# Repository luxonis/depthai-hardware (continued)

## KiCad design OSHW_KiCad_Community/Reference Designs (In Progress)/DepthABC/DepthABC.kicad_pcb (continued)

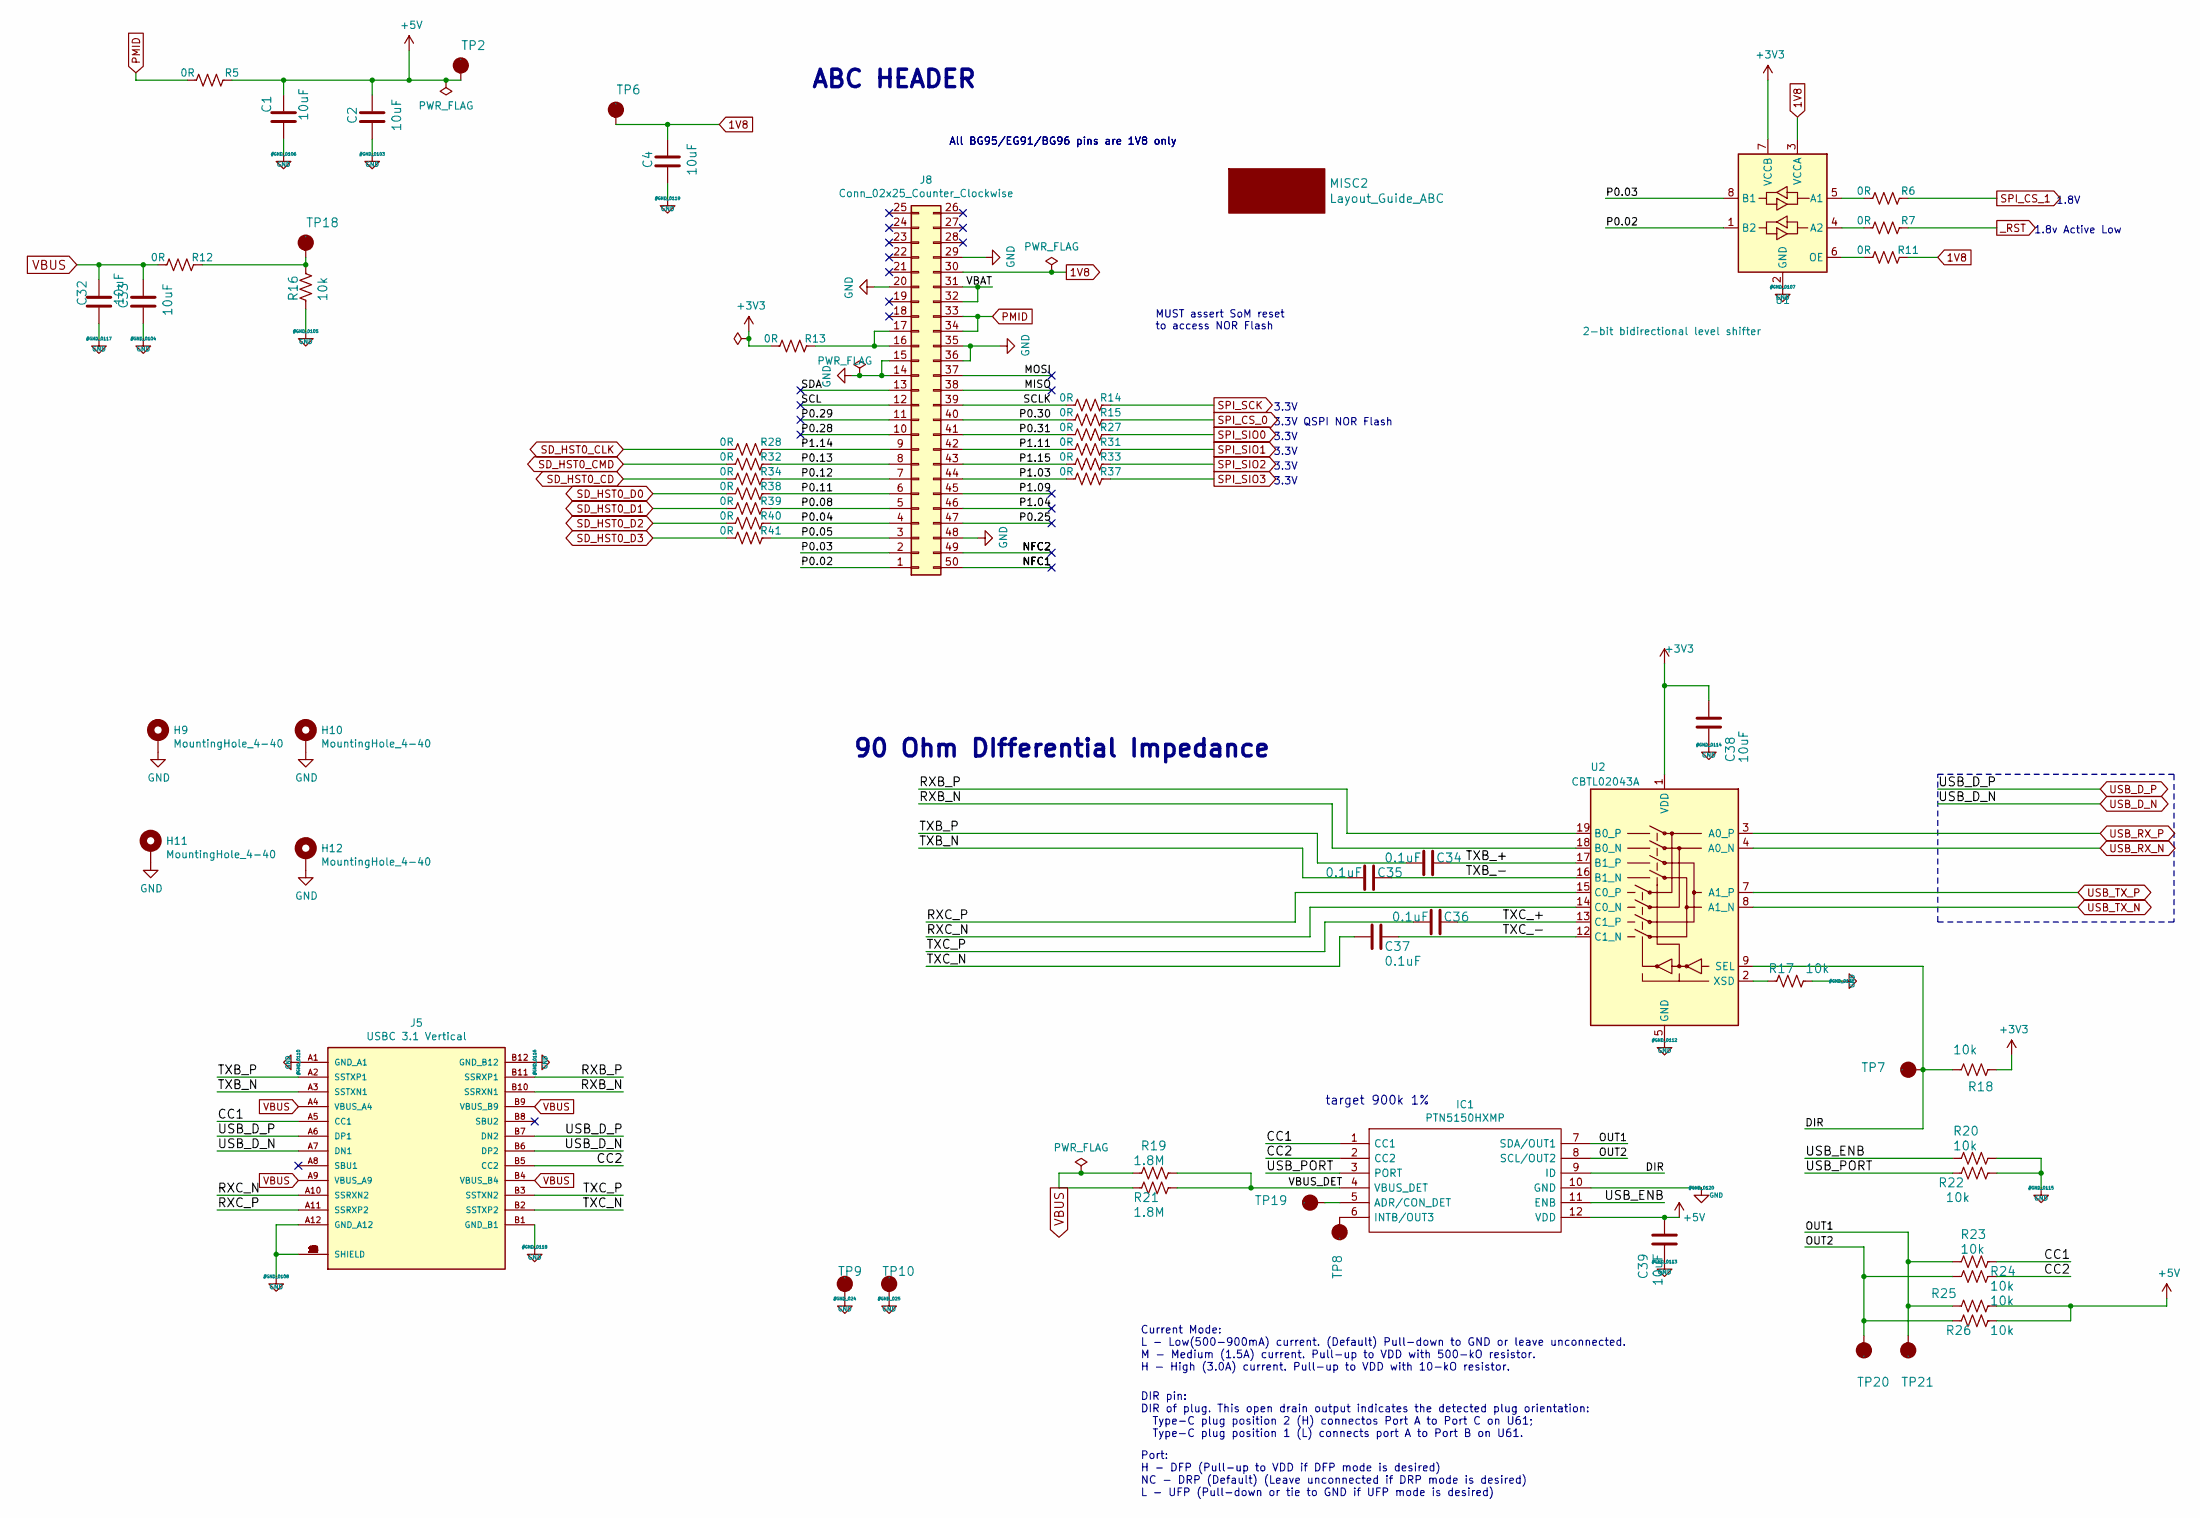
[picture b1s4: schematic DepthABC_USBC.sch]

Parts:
C1, C2, C4, C32, C33, C38, C39: 10uF; C_0603_1608Metric; Voltage Rating 6.3V; MPN1 C0603C106M8PAC7867
C34, C35, C36, C37: 0.1uF; C_0603_1608Metric; Voltage Rating 10V; MPN1 C0603C104K8RACTU
H9, H10, H11, H12: MountingHole_4-40; MountingHole_3mm_Pad
IC1: PTN5150HXMP; Manufacturer_Part_Number PTN5150HXMP; Mouser Part Number 771-PTN5150HXMP
J5: USBC 3.1 Vertical; AMPHENOL_10132328-10011LF; PARTREV A
J8: Conn_02x25_Counter_Clockwise; DF23C-50DS-0.5V(51); MPN1 DF23C-50DS-0.5V(51)
MISC2: Layout_Guide_ABC; ABC-Layout
R5, R6, R7, R11, R12, R13, R14, R15, R27, R28, R31, R32, R33, R34, R37, R38, R39, R40, R41: 0R; R_0603_1608Metric; Voltage Rating 1/10W; MPN1 RC0603FR-070RL
R16, R17, R18, R20, R22, R23, R24, R25, R26: 10k; R_0603_1608Metric; Voltage Rating 1/10W; MPN1 RC0603FR-7W10KL
R19, R21: 1.8M; R_0603_1608Metric; Voltage Rating 1/10W
TP2, TP6, TP7, TP8, TP9, TP10, TP18, TP19, TP20, TP21: TestPoint_Pad_D2.0mm
U1: 2-bit bidirectional level shifter; TSSOP-8_3x3mm_P0.65mm; MPN1 NTB0102DP-Q100H
U2: CBTL02043A; WQFN-20-1EP_2.5x4.5mm_P0.5mm_EP1x2.9mm; MPN1 CBTL02043ABQ,115

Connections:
1V8: C4.2, J8.30, R11.1, TP6.1, U1.3 (VCCA); also elsewhere on the board
+5V: C1.1, C2.2, C39.1, IC1.12 (VDD), R5.1, R25.1, R26.1, TP2.1; also elsewhere on the board
/USBC&POWER/CC1: IC1.1 (CC1), J5.A5 (CC1), R23.1
/USBC&POWER/CC2: IC1.2 (CC2), J5.B5 (CC2), R24.1
/USBC&POWER/DIR: IC1.9 (ID), R18.2, TP7.1, U2.9 (SEL)
/USBC&POWER/MISO: J8.38
/USBC&POWER/MOSI: J8.37
/USBC&POWER/NFC1: J8.50
/USBC&POWER/NFC2: J8.49
/USBC&POWER/OUT1: IC1.7 (SDA/OUT1), R23.2, R25.2, TP21.1
/USBC&POWER/OUT2: IC1.8 (SCL/OUT2), R24.2, R26.2, TP20.1
/USBC&POWER/P0.02: J8.1, U1.1 (B2)
/USBC&POWER/P0.03: J8.2, U1.8 (B1)
/USBC&POWER/P0.04: J8.4, R40.1
/USBC&POWER/P0.05: J8.3, R41.1
/USBC&POWER/P0.08: J8.5, R39.1
/USBC&POWER/P0.11: J8.6, R38.1
/USBC&POWER/P0.12: J8.7, R34.1
/USBC&POWER/P0.13: J8.8, R32.1
/USBC&POWER/P0.25: J8.47
/USBC&POWER/P0.28: J8.10
/USBC&POWER/P0.29: J8.11
/USBC&POWER/P0.30: J8.40, R15.2
/USBC&POWER/P0.31: J8.41, R27.2
/USBC&POWER/P1.03: J8.44, R37.2
/USBC&POWER/P1.04: J8.46
/USBC&POWER/P1.09: J8.45
/USBC&POWER/P1.11: J8.42, R31.2
/USBC&POWER/P1.14: J8.9, R28.1
/USBC&POWER/P1.15: J8.43, R33.2
/USBC&POWER/RXB_N: J5.B10 (SSRXN1), U2.18 (B0_N)
/USBC&POWER/RXB_P: J5.B11 (SSRXP1), U2.19 (B0_P)
/USBC&POWER/RXC_N: J5.A10 (SSRXN2), U2.14 (C0_N)
/USBC&POWER/RXC_P: J5.A11 (SSRXP2), U2.15 (C0_P)
/USBC&POWER/SCL: J8.12
/USBC&POWER/SCLK: J8.39, R14.2
/USBC&POWER/SDA: J8.13
/USBC&POWER/TXB_+: C34.1, U2.17 (B1_P)
/USBC&POWER/TXB_-: C35.1, U2.16 (B1_N)
/USBC&POWER/TXB_N: C35.2, J5.A3 (SSTXN1)
/USBC&POWER/TXB_P: C34.2, J5.A2 (SSTXP1)
/USBC&POWER/TXC_+: C36.1, U2.13 (C1_P)
/USBC&POWER/TXC_-: C37.1, U2.12 (C1_N)
/USBC&POWER/TXC_N: C37.2, J5.B2 (SSTXP2)
/USBC&POWER/TXC_P: C36.2, J5.B3 (SSTXN2)
/USBC&POWER/USB_ENB: IC1.11 (ENB), R20.2
/USBC&POWER/USB_PORT: IC1.3 (PORT), R22.2
/USBC&POWER/VBAT: J8.31, J8.32
/USBC&POWER/VBUS_DET: IC1.4 (VBUS_DET), R19.1, R21.1
unnamed: IC1.5 (ADR/CON_DET), TP19.1
unnamed: IC1.6 (INTB/OUT3), TP8.1
unnamed: J8.16, J8.17, R13.1
unnamed: R6.2, U1.5 (A1)
unnamed: R7.2, U1.4 (A2)
unnamed: R11.2, U1.6 (OE)
unnamed: R12.1, R16.2, TP18.1
unnamed: R17.2, U2.2 (XSD)
PMID: J8.33, J8.34, R5.2
SD_HST0_CD: R34.2; also elsewhere on the board
SD_HST0_CLK: R28.2; also elsewhere on the board
SD_HST0_CMD: R32.2; also elsewhere on the board
SD_HST0_D0: R38.2; also elsewhere on the board
SD_HST0_D1: R39.2; also elsewhere on the board
SD_HST0_D2: R40.2; also elsewhere on the board
SD_HST0_D3: R41.2; also elsewhere on the board
SPI_CS_0: R15.1; also elsewhere on the board
SPI_CS_1: R6.1; also elsewhere on the board
SPI_SCK: R14.1; also elsewhere on the board
SPI_SIO0: R27.1; also elsewhere on the board
SPI_SIO1: R31.1; also elsewhere on the board
SPI_SIO2: R33.1; also elsewhere on the board
SPI_SIO3: R37.1; also elsewhere on the board
USB_D_N: J5.A7 (DN1), J5.B6 (DP2); also elsewhere on the board
USB_D_P: J5.A6 (DP1), J5.B7 (DN2); also elsewhere on the board
USB_RX_N: U2.4 (A0_N); also elsewhere on the board
USB_RX_P: U2.3 (A0_P); also elsewhere on the board
USB_TX_N: U2.8 (A1_N); also elsewhere on the board
USB_TX_P: U2.7 (A1_P); also elsewhere on the board
VBUS: C32.1, C33.2, J5.A4 (VBUS_A4), J5.A9 (VBUS_A9), J5.B4 (VBUS_B4), J5.B9 (VBUS_B9), R12.2, R19.2, R21.2; also elsewhere on the board
_RST: R7.1; also elsewhere on the board

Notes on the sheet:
target 900k 1%
Current Mode: L - Low(500-900mA) current. (Default) Pull-down to GND or leave unconnected. M - Medium (1.5A) current. Pull-up to VDD with 500-kO resistor. H - High (3.0A) current. Pull-up to VDD with 10-kO resistor.
DIR pin: DIR of plug. This open drain output indicates the detected plug orientation: Type-C plug position 2 (H) connectos Port A to Port C on U61; Type-C plug position 1 (L) connects port A to Port B on U61.
Port: H - DFP (Pull-up to VDD if DFP mode is desired) NC - DRP (Default) (Leave unconnected if DRP mode is desired) L - UFP (Pull-down or tie to GND if UFP mode is desired)
All BG95/EG91/BG96 pins are 1V8 only
ABC HEADER
1.8V
3.3V
QSPI NOR Flash
MUST assert SoM reset to access NOR Flash
1.8v Active Low
90 Ohm DIfferential Impedance

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
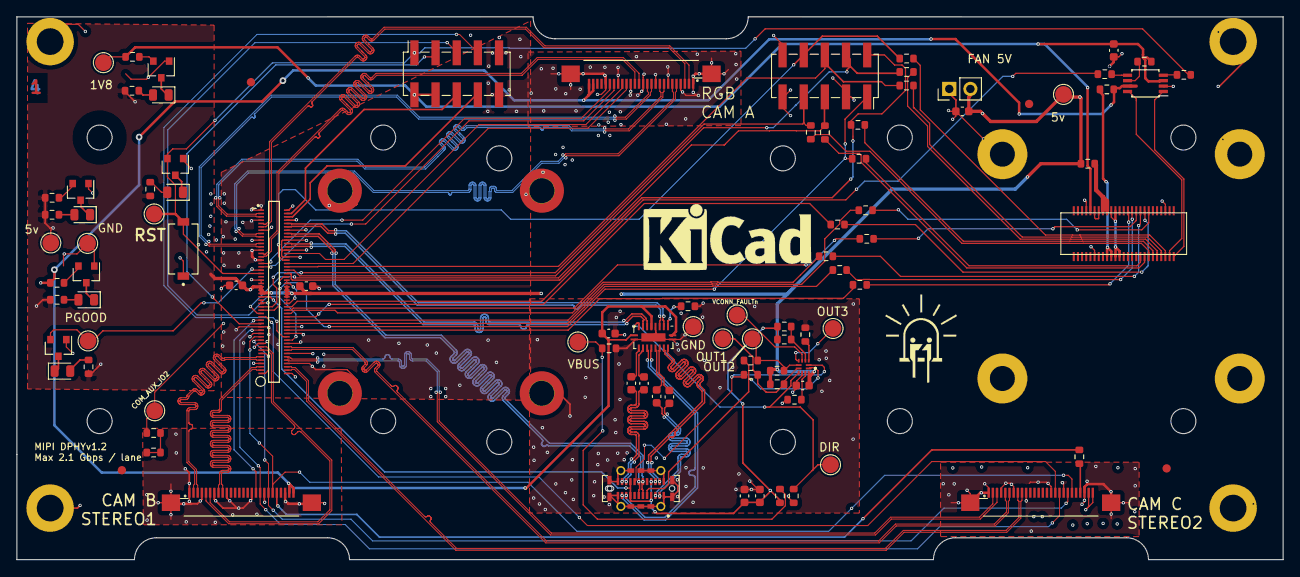
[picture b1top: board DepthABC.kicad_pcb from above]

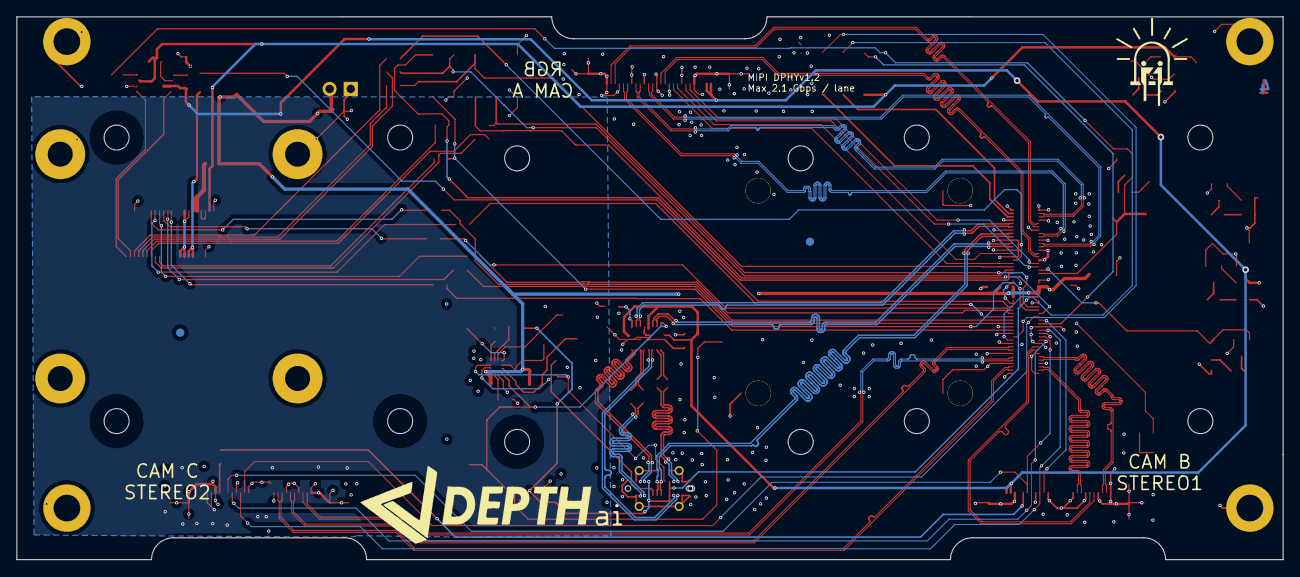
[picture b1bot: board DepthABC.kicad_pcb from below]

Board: 4 copper layers, 152.0 x 65.2 mm, 113 parts (5 on the bottom side), 125 nets.

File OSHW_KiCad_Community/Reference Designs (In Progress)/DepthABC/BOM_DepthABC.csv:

Component Count:,99,,,,,,,,,,,,
,,,,,,,,,,,,,
,,,,,,,,,,,,,
Collated Components:,,,,,,,,,,,,,
,,,,,,,,,,,,,
Item,Qty,Reference(s),Value,Footprint,Datasheet,Link1,MANUFACTURER,MPN1,Population,STANDARD,Short Description,Substitutes ,Voltage Rating
1,1,B1,"Off-Mohm, 50mA",depthABC:SW_PTS636_SM43J_SMTR_LFS,~,https://www.digikey.com/en/products/detail/c-k/PTS636-SM43-S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,C&K,PTS636,Y,~,reset switch,OR EQUIVALENT,~
2,8,"C1, C2, C3, C4, C32, C33, C38, C39",10uF ,Capacitor_SMD:C_0603_1608Metric,~,https://www.digikey.com/en/products/detail/kemet/C0603C106M8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,Kemet,C0603C106M8PAC7867,Y,X5R 20%,~,OR EQUIVALENT,6.3V
3,4,"C34, C35, C36, C37",0.1uF,Capacitor_SMD:C_0603_1608Metric,~,https://www.digikey.com/en/products/detail/kemet/C0603C104K8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,Kemet,C0603C104K8RACTU,Y,X5R 10%,~,OR EQUIVALENT,10V
4,3,"CAM1, CAM2, CAM3",Arducam_Module,Luxonis_KiCad_Master:arducam_40mm_34mm,~,~,Arducam,~,NO POP,~,~,~,~
5,3,"D1, D4, D5",RED,LED_SMD:LED_0805_2012Metric,~,https://www.digikey.com/en/products/detail/kingbright/APT201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,Kingbright,APT2012SRCPRV,Y,~,2V 0805 20mA test red LED,OR EQUIVALENT,~
6,2,"D2, D3",YELLOW,LED_SMD:LED_0805_2012Metric,~,https://www.digikey.com/en/products/detail/kingbright/APT201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,Kingbright,APT2012SYCK/J3-PRV,Y,~,2V 0805 20mA test orange LED,OR EQUIVALENT,~
7,6,"FID1, FID2, FID3, FID4, FID5, FID6",Fiducial,Fiducial:Fiducial_1mm_Mask2mm,~,~,~,~,~,~,~,~,~
8,4,"H1, H2, H3, H4",MountingHole_M3,MountingHole:MountingHole_3.2mm_M3_ISO7380_Pad,~,~,~,~,NO POP,~,Arducam mounts,~,~
9,4,"H5, H6, H7, H8",MountingHole_Pad,Luxonis_KiCad_Master:Mounting_Wuerth_WA-SMSI-M2_H3mm_9774030243,~,https://www.digikey.com/en/products/detail/9774030243R/732-7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,Wuerth,9774030243R,Y,~,SoM Mount,~,~
10,4,"H9, H10, H11, H12",MountingHole_4-40,MountingHole:MountingHole_3mm_Pad,~,~,~,~,NO POP,~,ABC mount,~,~
11,1,IC1,PTN5150HXMP,Luxonis_KiCad_Master:PTN5150HXMP,http://www.nxp.com/docs/en/data-sheet/PTN5150A.pdf,https://www.digikey.com/en/products/detail/nxp-usa-inc/PTN51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,NXP,PTN5150HXMP,Y,~,Usb port control,N,
12,2,"J1, J4",Conn_02x05_Odd_Even,Connector_PinSocket_2.54mm:PinSocket_2x05_P2.54mm_Vertical_SMD,~,~,~,~,NO POP,~,2x05 FEMALE 2.54mm pin socket,~,~
13,1,J2,FAN,Connector_PinHeader_2.54mm:PinHeader_1x02_P2.54mm_Vertical,~,~,~,~,NO POP,~,~,~,~
14,1,J3,BW1099EMB_SoM,Luxonis_KiCad_Master:DF40HC(3.0)-100DS-0.4V(58),https://www.hirose.com/product/document?clcode=CL0684-4003-3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,https://www.mouser.com/ProductDetail/Hirose-Connector/DF40HC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,Amphenol,DF40HC(3.0)-100DS-0.4V(58),Y,~,SoM header,N,~
15,1,J5,USBC 3.1 Vertical,AMPHENOL_10132328-10011LF,,https://www.amphenol-icc.com/usb-1013232810011lf.html?__cf_c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,Amphenol,10132328-10011LF,Y,~,~,N,~
16,3,"J6, J7, J9",26_pin_FFC,Luxonis_KiCad_Master:F32R-26p-FFC,,https://www.mouser.com/ProductDetail/Amphenol-ICC-Aorora/F32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,Amphenol,F32R-1A7H1-11026,Y,~,DM Series Luxonis FFC,N,~
17,1,J8,Conn_02x25_Counter_Clockwise,ABC:DF23C-50DS-0.5V(51),~,https://www.mouser.com/ProductDetail/Hirose-Connector/DF23C-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,Amphenol,DF23C-50DS-0.5V(51),Y,~,ABC header,N,~
18,1,MISC1,Layout_Guide_BW1099,Luxonis_KiCad_Master:BW1099_Layout_Guide,~,~,Luxonis,~,NO POP,~,~,~,~
19,1,MISC2,Layout_Guide_ABC,ABC:ABC-Layout,~,~,Luxonis,~,NO POP,~,~,~,~
20,5,"Q1, Q2, Q3, Q4, Q5",RK7002B,Package_TO_SOT_SMD:SOT-23,https://media.digikey.com/pdf/Data%20Sheets/Rohm%20PDFs/RK7002B.pdf,https://www.digikey.com/en/products/detail/rohm-semiconducto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,ROhm,,Y,~,2.5V Drive Nch FET ESD Protection Diode,W/ APPROVAL,60V 250mA
21,6,"R1, R2, R3, R4, R30, R36",10,Resistor_SMD:R_0603_1608Metric,~,https://www.digikey.com/en/products/detail/rohm-semiconducto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,ROhm,ESR03EZPF10R0,Y,1%,~,OR EQUIVALENT,1/10W
22,21,"R5, R6, R7, R9, R10, R11, R12, R13, R14, R15, R27, R28, R31, R32, R33, R34, R37, R38, R39, R40, R41",0R,Resistor_SMD:R_0603_1608Metric,~,https://www.digikey.com/en/products/detail/yageo/RC0603FR-07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,Yageo,RC0603FR-070RL,Y,~,~,OR EQUIVALENT,1/10W 
23,10,"R8, R16, R17, R18, R20, R22, R23, R24, R25, R26",10k,Resistor_SMD:R_0603_1608Metric,~,https://www.digikey.com/en/products/detail/yageo/RC0603FR-7W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,Yageo,RC0603FR-7W10KL,Y,1%,~,OR EQUIVALENT,1/10W 
24,2,"R19, R21",1.8M,Resistor_SMD:R_0603_1608Metric,~,~,~,~,Y,1%,~,OR EQUIVALENT,1/10W
25,2,"R29, R35",1k,Resistor_SMD:R_0603_1608Metric,~,https://www.digikey.com/en/products/detail/koa-speer-electro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,KOA,SG73S1JTTD1001F,Y,1%,~,OR EQUIVALENT,1/10W
26,1,U1,2-bit bidirectional level shifter ,Package_SO:TSSOP-8_3x3mm_P0.65mm,http://www.ti.com/lit/ds/symlink/txb0102.pdf,https://www.digikey.com/en/products/detail/nxp-usa-inc/NTB01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,NXP,NTB0102DP-Q100H,Y,~,~,OR EQUIVALENT,~
27,1,U2,CBTL02043A,Package_DFN_QFN:WQFN-20-1EP_2.5x4.5mm_P0.5mm_EP1x2.9mm,https://www.nxp.com/docs/en/data-sheet/CBTL02043A_CBTL02043B.pdf,https://www.digikey.com/en/products/detail/nxp-usa-inc/CBTL0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,NXP,"CBTL02043ABQ,115",Y,~,Usb mux,N,

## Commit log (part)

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2023-01-07 Typo fix
2023-01-07 boot mode fix eMMC
2023-01-16 new datasheet
2023-01-16 OAK-SoM MAX updates
2023-01-18 Added mqtt support to POE docs
2023-01-18 Removed multi-cam-support branch from docs
2023-01-19 Update ar0234.rst
    Tested on FFC-4P and we seem to support 60 FPS.
2023-01-23 Fixed max FPS for IMX214 from 60fps to 35fps
2023-01-23 Update NG9097pro.rst
    broken link fix
2023-01-24 Projector temeprature update docs
2023-01-24 Updated LCM48/IMX582 docs
2023-01-24 Updated CCM specs
2023-01-25 Fixed M8 usb connection description
2023-01-25 Added HW blocks docs for RVC2
2023-01-26 Added OAK FFC Kit to docs. Renamed file
2023-01-30 Updated products' key features
2023-02-01 Updated poe s2 connectors in docs
2023-02-04 Added advance poe settings docs
2023-02-04 Added docs on AF/FF querying info with depthai
2023-02-06 Fixed some urls/refs, removed copyright
2023-02-08 Added poe injector to the list of docs
2023-02-11 broken sentence rmoved
2023-02-13 removed pdf building RTD - potentially fixing failing docs build
2023-02-14 SR and LR added to OAK-D CE
2023-02-14 new photos
2023-02-14 TODO: add redirections for /index.html#all-in-one-dev-kit-designs and /index.html#miscellaneous-designs to /index.html#other-designs
2023-02-14 new thumbnails
2023-02-14 cropped images
2023-02-14 bg removed
2023-02-15 Added oak-d-pro TH img
2023-02-15 Temp fix for oak-d-pro thumbnail pic
2023-02-16 photo swap
2023-02-17 Updated performance docs
2023-02-20 Updated favicon
2023-02-21 OAK-D-LR & SR added to index
2023-02-22 Updated calibration docs
2023-02-28 Updated the files to R3M1E4
2023-03-01 Updated oak-d-sr minZ
    (cherry picked from commit 54b8ce719f3469f9dd66256d9fc4b3c52be31205)
2023-03-04 Updated supported sensors docs
2023-03-06 Updated time diagrams for FSYNC
2023-03-06 Added code snippet for FFC-4P syncing between 4-lane and 2-lane MIPI groups
2023-03-08 Upload OAK-D-S2 enclosure stl files
2023-03-08 Upload OAK-D_enclosure stp file
2023-03-08 Upload OAK-D-LITE_enclosure stp file
2023-03-08 Upload OAK-1_enclosure STL file
2023-03-08 Upload OAK-1-POE-enclosure STL file
2023-03-08 Upload OAK-1-Lite_enclosure .STL file
2023-03-08 Upload OAK-D-S2-POE_enclosure.STL file
2023-03-08 Upload OAK-D-CM4-POE_enclosure.STL file
2023-03-08 Upload y-adapter.STL file
2023-03-08 Added IMX582-RAM doc snippet to OAK-1-Max and IMX582 docs pages
2023-03-14 Updated depth perception (minz/maxz/optimal) for all OAK-D* models
2023-03-15 Updated rvc3 docs (main features)
2023-03-22 updated oak-d-lite encsloure
2023-03-27 Updated device features (rvc2) for OAK-1 cams
2023-03-27 Updated supported sensors page, added IMX296, IMX219
2023-04-03 correction connector A pin32 -- RTC_INT
2023-04-03 Updated docs so ov9782 supports 400p (120fps)
2023-04-04 Add shop link for OAK-D-PCBA
2023-04-04 Added docs on how to replace oak som pro versions
2023-04-11 Updated OAK-D-LR FOV values
2023-04-19 Update calibration.rst
    Update calibration.rst with new calibration process
2023-04-21 Fixing ext trigger schematics
2023-04-25 Added FFC-Kit adapters
2023-04-26 merged SPI and RTC fixes
2023-04-26 SOM PRO - added note that changing rvc2 to rvc3 not officially supported by Luxonis
2023-05-05 Added imgs to docs
2023-05-05 Added OAK-FFC-4P-POE docs page. Moved FFC-6P to other devices
2023-05-06 Updated OAK-FFC 1P PoE page and images
2023-05-08 Added docs section about using RPI cameras to FFC baseboards
2023-05-10 Fix IMX582 HFOV / DFOV
2023-05-11 Moved enclosure files (step/stl) to digitalocean as well (previously it was only PCBAs)
2023-05-18 128Mbit NOR
2023-05-19 Initial release of OAK-D-SR-POE
2023-05-19 Added OAK-D-SR-POE docs
2023-05-23 Uploaded FFC-6P and FFC-4P-POE adapters for FFC-Kit
2023-06-02 Updated imgs
2023-06-02 OAK-D-Lite thermal tests
2023-06-03 Added CCM thermal heating to docs
2023-06-04 Updated docs, added link
2023-06-13 Updated FFC-6P docs (dimensions & weight)
2023-06-14 Updated readthedocs.yaml
2023-06-14 Updated yaml
2023-06-14 Revert "Updated yaml"
    This reverts commit 0b040243d894fd137d77818ec4c8efbec9f4ca6e.
2023-06-14 Updated max FPS at 720p and 800p for OV9x82 sensors, as support was added for 120fps (previously max 60fps)
2023-06-19 Updated dot projector docs
2023-06-20 PoE device USB2.0 spcs fix
2023-06-21 Added img
2023-06-22 Added low-light comparison photo
2023-06-23 trd yaml update
2023-06-26 Updated sensor resolution modes in docs
2023-06-26 Added initial release of PA0960_R0M0E0 of FFC-IR
2023-06-26 Updated DM0260 to revision R2M1E1
    Missing pictures of new revision boards.
2023-06-27 Added .STEP 3d model to 3D_Models folder
2023-06-27 Update README.md, changed Altium designer from 22 to 23
2023-06-27 Added BOM files to DOCS
    Added BOM files to projects:
    - PA0960
    - DM0260 for 1V0 and 1V2
    - OAK-D-SR-PoE for EL2086 and EL6905
2023-06-30 Updated FFC camera modules images
2023-07-03 Enable pdf generation
2023-07-05 Add files via upload
    added enclosure step file
2023-07-06 Removed unicode '❌' as it fails to render to PDF
2023-07-24 Update OV9282 FOV (89 DFOV, 80HFOV)
2023-07-26 Fixed typo, update oak-d-pro-w-poe img
2023-08-01 Updated POE troubleshooting
2023-08-16 Updated readthedocs.yaml, as they decided to deprecate some functions yet again for absolutely no good reason
2023-08-16 Updated available CCMs page
2023-08-24 Updated docs for oak-ffc-4p-poe
2023-09-01 Files for M8 programming board, fabricaation files in folder Docs, PCB in forder PCB
2023-09-01 Initial push
    Added Production files in the folder Docs. Added PCB files in folder PCB. Added .STEP of DM370
2023-09-01 Updated SOM-PRO NOR flash to 32MB
2023-09-01 Updated CCMs used for mono cameras in Pro devices
2023-09-01 Fixed old revision of Schematic.pdf and added files from GDrive to be shure it is the latest revision
2023-09-01 updated readme, referencing DM0260
2023-09-01 Updated docs to include some additional HW docs, fixed formatting, specified factory reset info
2023-09-05 Added rae readme
2023-09-05 Updated charuco boards
2023-09-13 Updated OAK-D-LR 3D models
2023-09-18 Update docs
2023-09-20 Remove distortion params, as we do on-device undistortion/dewarping
2023-09-25 Update rvc4 AI performance/power ocnsumption
2023-09-28 Update AR0234 driver specs, as we have updated driver on develop branch
2023-10-03 Bump urllib3 from 1.26.15 to 1.26.17 in /docs
    Bumps [urllib3](https://github.com/urllib3/urllib3) from 1.26.15 to 1.26.17.
    - [Release notes](https://github.com/urllib3/urllib3/releases)
    - [Changelog](https://github.com/urllib3/urllib3/blob/main/CHANGES.rst)
    - [Commits](https://github.com/urllib3/urllib3/compare/1.26.15...1.26.17)
    ---
    updated-dependencies:
2023-10-03 Added FOV calc links to RAE, and to all Rectified Depth FOV
2023-10-09 Update CCM section
2023-10-11 Updated FFC-4P docs
2023-10-18 Bump urllib3 from 1.26.15 to 1.26.18 in /docs
    Bumps [urllib3](https://github.com/urllib3/urllib3) from 1.26.15 to 1.26.18.
    - [Release notes](https://github.com/urllib3/urllib3/releases)
    - [Changelog](https://github.com/urllib3/urllib3/blob/main/CHANGES.rst)
    - [Commits](https://github.com/urllib3/urllib3/compare/1.26.15...1.26.18)
    ---
    updated-dependencies:
2023-10-20 Added power usage docs to all rvc2 devices
2023-10-20 Added max operating temp to all rvc2 devices
2023-10-21 RPI 15pin adapter
    Added project files for OAK-FFC to 15pin RPI FFC adapter
2023-10-23 adapter connection
    added connection photo
2023-10-23 Uploaded model to DO
2023-10-23 Moved step files to DO
2023-10-23 Added docs for FSYNC Y-adapter accessory
2023-10-23 Added initial depth accuracy docs for OAK-D-Lite and 800P 75mm baseline OAK-Ds
2023-10-25 Update imx296 docs on color artifacts
2023-10-26 Added an image to the vibration docs
2023-10-26 Fixed depth accuracy docs for the OAk-D Pro W
2023-10-27 Update DM1097.rst
    Added link to RPI OS image.
2023-10-30 Fixed url inside device comparison
2023-10-30 Added IMU info to docs for the OAK-D-LR
2023-10-31 Removed getting started rae docs
2023-11-08 Added fsync example for 4 cameras
2023-11-08 Updated FSYNC schematics, added PCBA schematics img (about BNC to M8 connector)
2023-11-13 Added SR-POE EFL
2023-11-14 Updating docs - sensors
2023-11-16 Updated rae/LR shop links
2023-11-21 Update IMX378W VFOV (70°->74°)
2023-11-28 Updated depth accuracy docs
2023-11-28 Updated requirements.txt
2023-12-01 Updating calibration guide
2023-12-11 Added OAK-T docs page
2023-12-11 Updated some old docs and formatting
2023-12-12 Downscaled imgs to reduce size
2023-12-12 Added OAK-D-LR dimensions (technical drawing)
2023-12-20 Updated oak-som-pro docs
2023-12-22 Added poe connectivity drop section
2024-01-04 Multiple net adapters for POE docs
2024-01-07 Updated operating temperature docs
2024-01-11 Bump jinja2 from 3.0.3 to 3.1.3 in /docs
    Bumps [jinja2](https://github.com/pallets/jinja) from 3.0.3 to 3.1.3.
    - [Release notes](https://github.com/pallets/jinja/releases)
    - [Changelog](https://github.com/pallets/jinja/blob/main/CHANGES.rst)
    - [Commits](https://github.com/pallets/jinja/compare/3.0.3...3.1.3)
    ---
    updated-dependencies:
2024-01-16 Fix IMX582 CCM number
2024-01-17 Fix CCM specs for IMX214 normal FOV (AF/FF)
2024-01-20 Updated OAK-T images
2024-01-22 Fix oak-t focus range
2024-01-23 Update RPi docs
2024-01-23 Testing out sphinx-charts
2024-01-24 Updated some device names
2024-01-24 Fix POE s2 cameras
2024-01-25 Updated rae docs about blobconverter url
2024-01-26 Updated docs about SR-POE M8 connector. Future devices will have similar schematics
2024-01-26 Decrease amount of data, perhaps that's the issue
2024-01-26 Revert "moved json"
    This reverts commit 92f08ab80f8459bcecea4fc4d2af3038bc6531cb.
2024-01-27 Revert "Moved chart json once again"
    This reverts commit 4a6ae119dce523b37ede55a288124dcbe2dd7b93.
2024-01-29 Added psrbs connector specs to ffc-4p
2024-01-29 sphinx-charts (#473)
    * Testing out sphinx-charts
    * Update chart path
    * Decrease amount of data, perhaps that's the issue
    * moved json
    * Revert "moved json"
    This reverts commit 92f08ab80f8459bcecea4fc4d2af3038bc6531cb.
2024-01-29 Updated path for json
2024-01-30 Updating camera sensor docs
2024-01-30 Fixing double text
2024-02-01 Hardware docs index update
2024-02-05 Updated ffc-4p psrbs connector
2024-02-05 Added OAK-T enclosure 3d files (step/stl)
2024-02-06 Update README.md
    Added picture to readme.md file.
2024-02-06 Update README.md
    added back-view image.
2024-02-06 Update README.md
    Added front-view image.
2024-02-06 Initial commit of OAK-T files. (#477)
    * initial commit of OAK-T files.
    New device, OAK-T added to the docs for the community to access it.
    * Update README.md
    Added picture to readme.md file.
    * Update README.md
    Added backview image.
2024-02-09 Moved CCMs specs to its docs
2024-02-14 Updated 800p json, trunctu
2024-02-22 Update y-adapter docs to include voltage requirement
2024-02-29 Fix broken thumbnail images, added video on how to replace ccms
2024-02-29 Started writing docs about depth accuracy oscillation
2024-02-29 Added OAK-D-LR changing lens video
2024-03-02 Added Jetson docs (#478)
2024-03-04 Y8-adapter added
    Y8-adapter files and readme added
2024-03-04 Updated fsync y-adapter readme and moved 3d files to digitalocean
2024-03-05 Update dot projector docs to viewer (instead of demo)
2024-03-06 Updated RPi camera adapter links
2024-03-08 Removed url for gdocs about depth accuracy
2024-03-14 passive poe docs
2024-03-14 Added ™ simbol to realsense
2024-03-21 Updated rvc2 encoding features
2024-04-18 Fix sr-poe ip rating to ip66
2024-04-22 Update multiple ffc-tof-33d
2024-05-02 Update TOF so that its 45fps and max 6m
2024-05-06 Bump jinja2 from 3.0.3 to 3.1.4 in /docs
    Bumps [jinja2](https://github.com/pallets/jinja) from 3.0.3 to 3.1.4.
    - [Release notes](https://github.com/pallets/jinja/releases)
    - [Changelog](https://github.com/pallets/jinja/blob/main/CHANGES.rst)
    - [Commits](https://github.com/pallets/jinja/compare/3.0.3...3.1.4)
    ---
    updated-dependencies:
2024-05-22 Updated OAK-FFC-1-POE schematics/outputs to latest revision (R4)
2024-05-28 Updated OAK-FFC-1-POE schematics/outputs to latest revision (R4) (#482)
    * Updated OAK-FFC-1-POE schematics/outputs to latest revision (R4)
    * Updated readme
    * Revert "Updated readme"
    This reverts commit cd02c1515a098f74d5e9b29d918d68c244fbe1a1.
2024-06-18 OAK-D-LR update
    Updated readme, PCB, Docs, missing 3D model.
2024-06-20 OAK-FFC 4P
    Updated to revision R7M1E7, missing correct 3D model
2024-06-26 OAK-FFC-CBA (without 3d model)
2024-09-24 Remove docs folder (#486)
2024-10-15 Removed unnecessary whitespace
2024-12-19 Update OAK-D-Lite PCBA step file
